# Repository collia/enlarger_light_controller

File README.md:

# enlarger_light_controller

Device that upgrates enlarger head
It based on stm32 blue pill board, spi controlled 7-led indicator, several buttons and encoders, and RGB leds.

It is build in github.com/collia/stm32scons.git environment

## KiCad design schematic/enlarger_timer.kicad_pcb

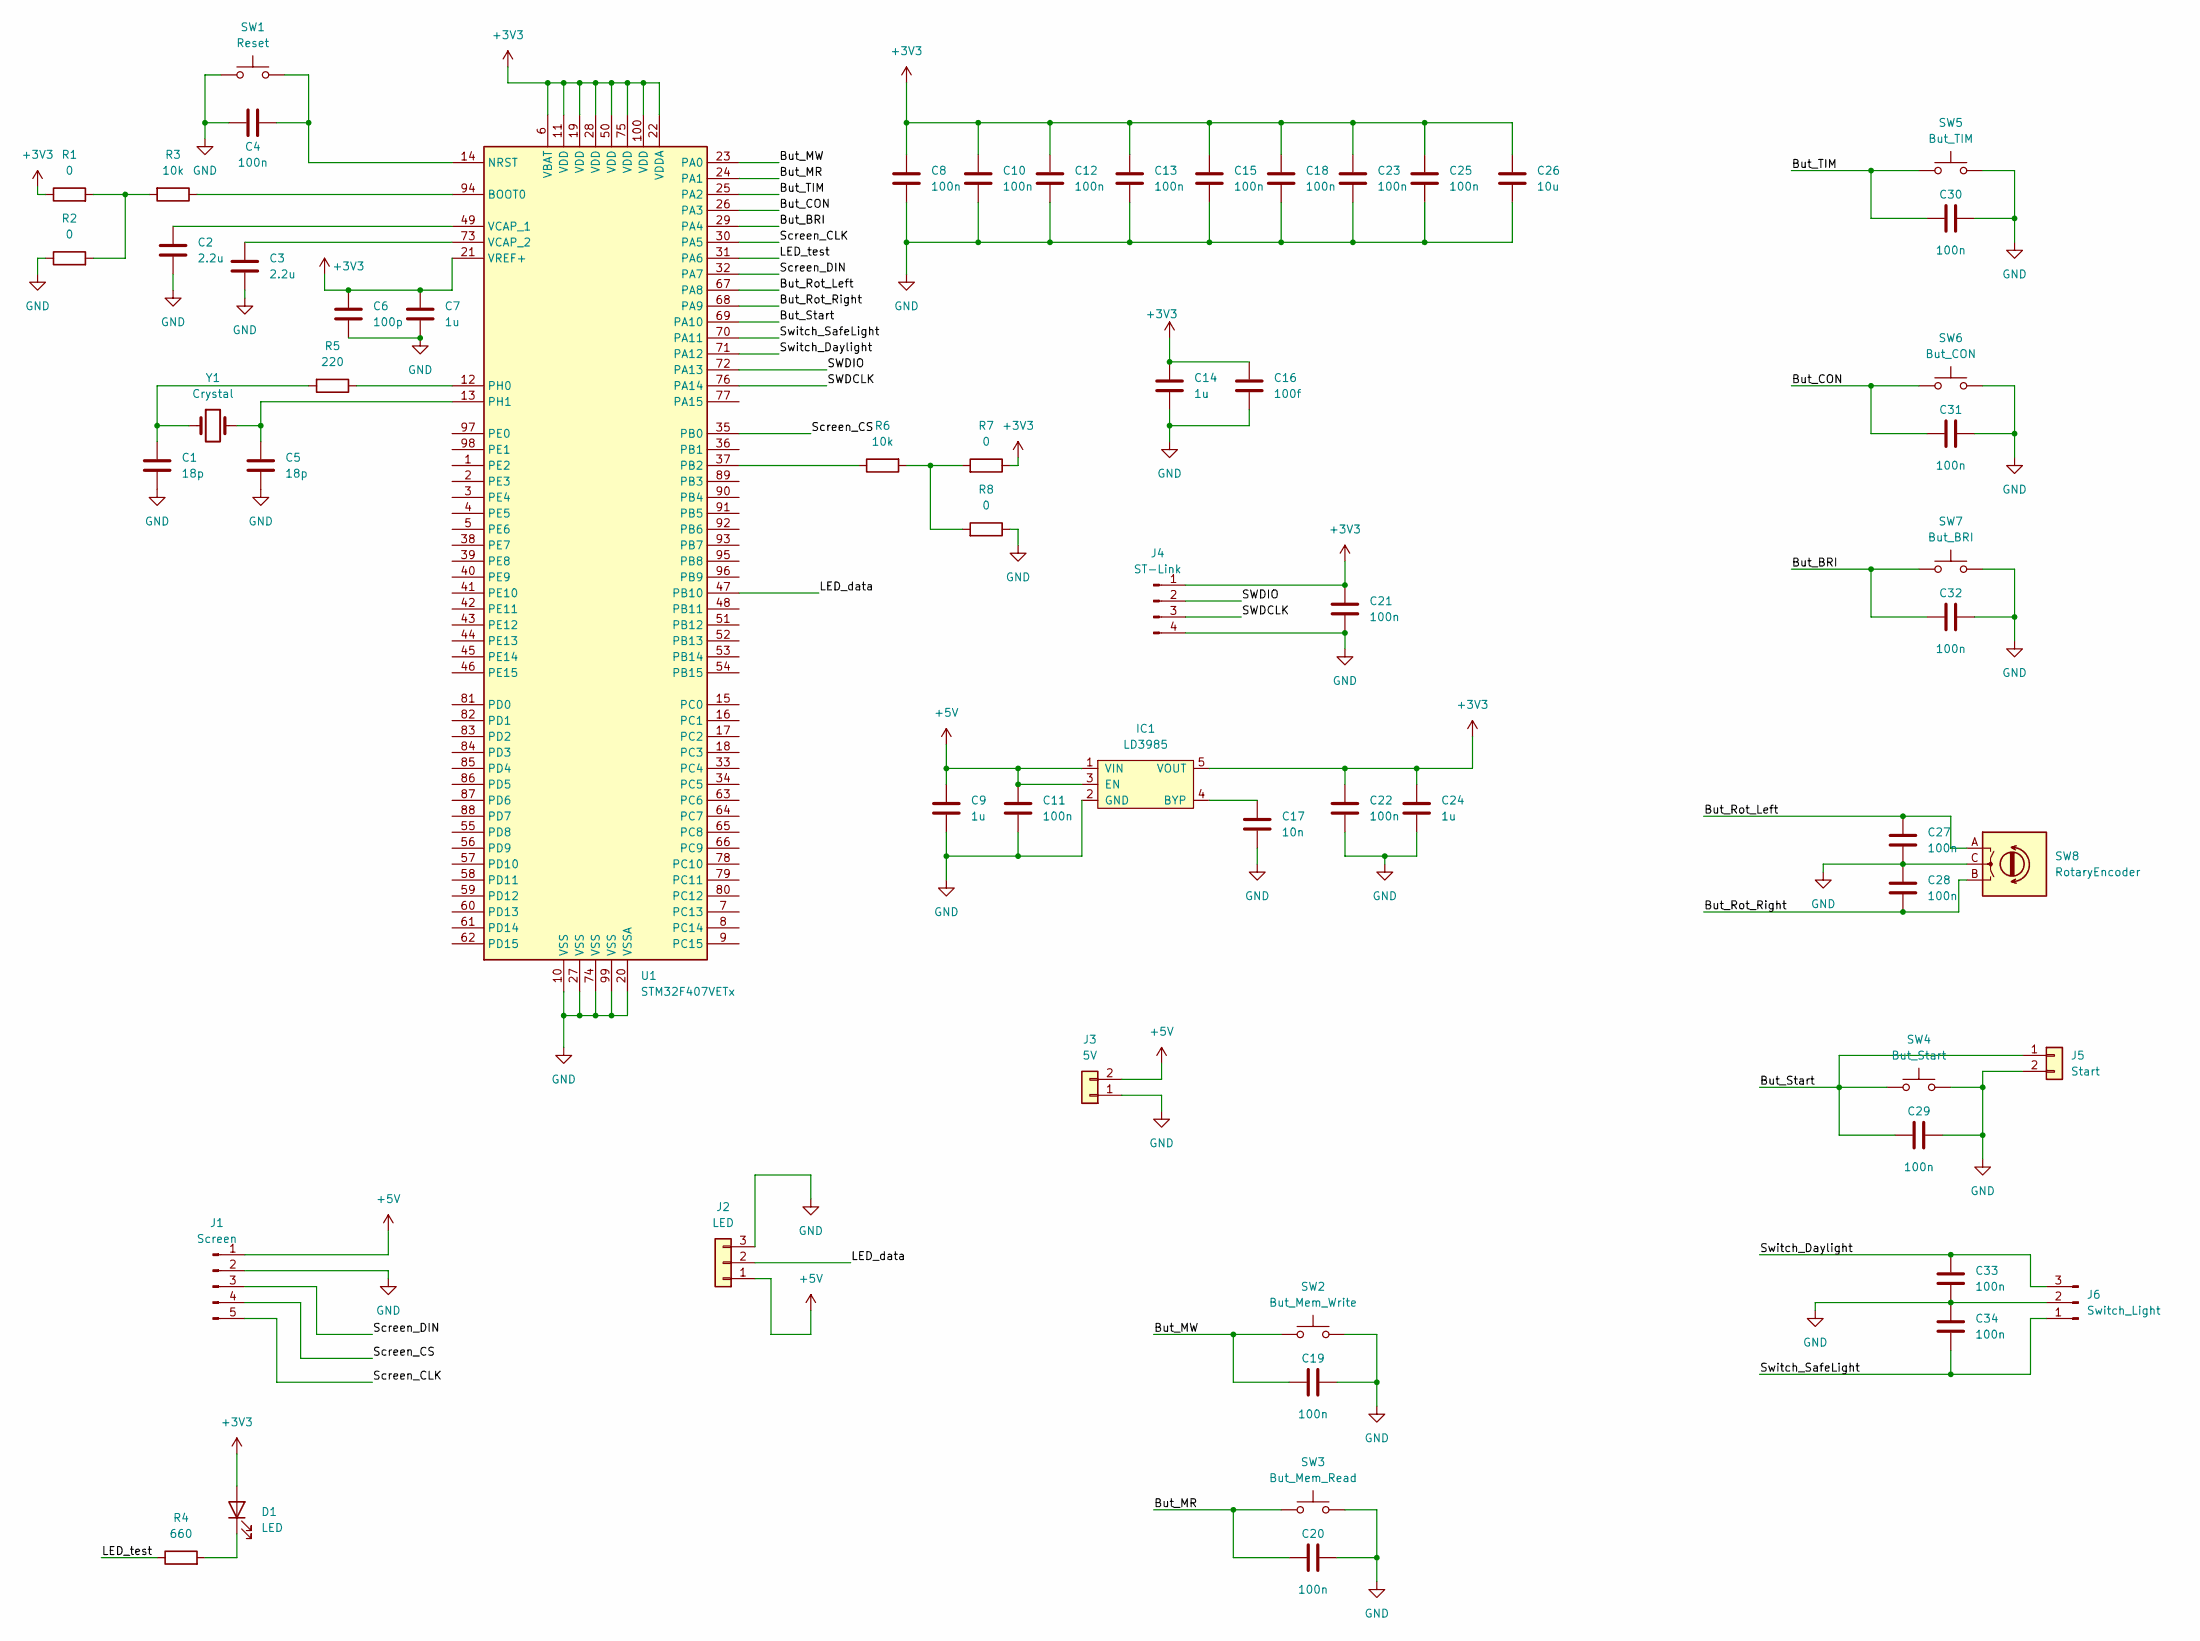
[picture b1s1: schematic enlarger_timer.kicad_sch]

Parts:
C1, C5: 18p; C_0805_2012Metric
C2, C3: 2.2u; C_0805_2012Metric
C4, C8, C10, C11, C12, C13, C15, C18, C19, C20, C21, C22, C23, C25, C27, C28, C29, C30, C31, C32, C33, C34: 100n; C_0805_2012Metric
C6: 100p; C_0805_2012Metric
C7, C9, C14, C24: 1u; C_0805_2012Metric
C16: 100f; C_0805_2012Metric
C17: 10n; C_0805_2012Metric
C26: 10u; C_0805_2012Metric
D1: LED; D_0805_2012Metric
IC1: LD3985; SOT-23-5_HandSoldering; Farnell 3130019
J1: Screen; PinHeader_1x05_P2.54mm_Horizontal
J2: LED; JST_EH_S3B-EH_1x03_P2.50mm_Horizontal
J3: 5V; PinHeader_1x02_P2.54mm_Horizontal
J4: ST-Link; PinHeader_1x04_P2.54mm_Horizontal
J5: Start; JST_EH_S2B-EH_1x02_P2.50mm_Horizontal
J6: Switch_Light; PinHeader_1x03_P2.54mm_Horizontal
R1, R2, R7, R8: 0; R_0805_2012Metric
R3, R6: 10k; R_0805_2012Metric
R4: 660; R_0805_2012Metric
R5: 220; R_0805_2012Metric
SW1: Reset; SW_Push_1P1T_NO_6x6mm_H9.5mm
SW2: But_Mem_Write; SW_Push_1P1T_NO_6x6mm_H9.5mm
SW3: But_Mem_Read; SW_Push_1P1T_NO_6x6mm_H9.5mm
SW4: But_Start; SW_Push_1P1T_NO_6x6mm_H9.5mm
SW5: But_TIM; SW_Push_1P1T_NO_6x6mm_H9.5mm
SW6: But_CON; SW_Push_1P1T_NO_6x6mm_H9.5mm
SW7: But_BRI; SW_Push_1P1T_NO_6x6mm_H9.5mm
SW8: RotaryEncoder; SMD_Encoder
U1: STM32F407VETx; LQFP-100_14x14mm_P0.5mm
Y1: Crystal; Crystal_HC18-U_Vertical

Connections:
+3V3: C6.1, C7.1, C8.1, C10.1, C12.1, C13.1, C14.1, C15.1, C16.1, C18.1, C21.1, C22.1, C23.1, C24.1, C25.1, C26.1, D1.2 (A), IC1.5 (VOUT), J4.1, R1.1, R7.1, U1.6 (VBAT), U1.11 (VDD), U1.19 (VDD), U1.21 (VREF+), U1.22 (VDDA), U1.28 (VDD), U1.50 (VDD), U1.75 (VDD), U1.100 (VDD)
+5V: C9.1, C11.1, IC1.1 (VIN), IC1.3 (EN), J1.1, J2.1, J3.2
/But_BRI: C32.1, SW7.1, U1.29 (PA4)
/But_CON: C31.1, SW6.1, U1.26 (PA3)
/But_MR: C20.1, SW3.1, U1.24 (PA1)
/But_MW: C19.1, SW2.1, U1.23 (PA0)
/But_Rot_Left: C27.1, SW8.A, U1.67 (PA8)
/But_Rot_Right: C28.2, SW8.B, U1.68 (PA9)
/But_Start: C29.1, J5.1, SW4.1, U1.69 (PA10)
/But_TIM: C30.1, SW5.1, U1.25 (PA2)
/LED_data: J2.2, U1.47 (PB10)
/LED_test: R4.1, U1.31 (PA6)
/SWDCLK: J4.3, U1.76 (PA14)
/SWDIO: J4.2, U1.72 (PA13)
/Screen_CLK: J1.5, U1.30 (PA5)
/Screen_CS: J1.4, U1.35 (PB0)
/Screen_DIN: J1.3, U1.32 (PA7)
/Switch_Daylight: C33.1, J6.3, U1.71 (PA12)
/Switch_SafeLight: C34.2, J6.1, U1.70 (PA11)
GND: C1.2, C2.2, C3.2, C4.1, C5.2, C6.2, C7.2, C8.2, C9.2, C10.2, C11.2, C12.2, C13.2, C14.2, C15.2, C16.2, C17.2, C18.2, C19.2, C20.2, C21.2, C22.2, C23.2, C24.2, C25.2, C26.2, C27.2, C28.1, C29.2, C30.2, C31.2, C32.2, C33.2, C34.1, IC1.2 (GND), J1.2, J2.3, J3.1, J4.4, J5.2, J6.2, R2.1, R8.1, SW1.1, SW2.2, SW3.2, SW4.2, SW5.2, SW6.2, SW7.2, SW8.C, U1.10 (VSS), U1.20 (VSSA), U1.27 (VSS), U1.74 (VSS), U1.99 (VSS)
unnamed: C1.1, R5.2, Y1.1
unnamed: C2.1, U1.49 (VCAP_1)
unnamed: C3.1, U1.73 (VCAP_2)
unnamed: C4.2, SW1.2, U1.14 (NRST)
unnamed: C5.1, U1.13 (PH1), Y1.2
unnamed: C17.1, IC1.4 (BYP)
unnamed: D1.1 (K), R4.2
unnamed: R1.2, R2.2, R3.2
unnamed: R3.1, U1.94 (BOOT0)
unnamed: R5.1, U1.12 (PH0)
unnamed: R6.1, U1.37 (PB2)
unnamed: R6.2, R7.2, R8.2

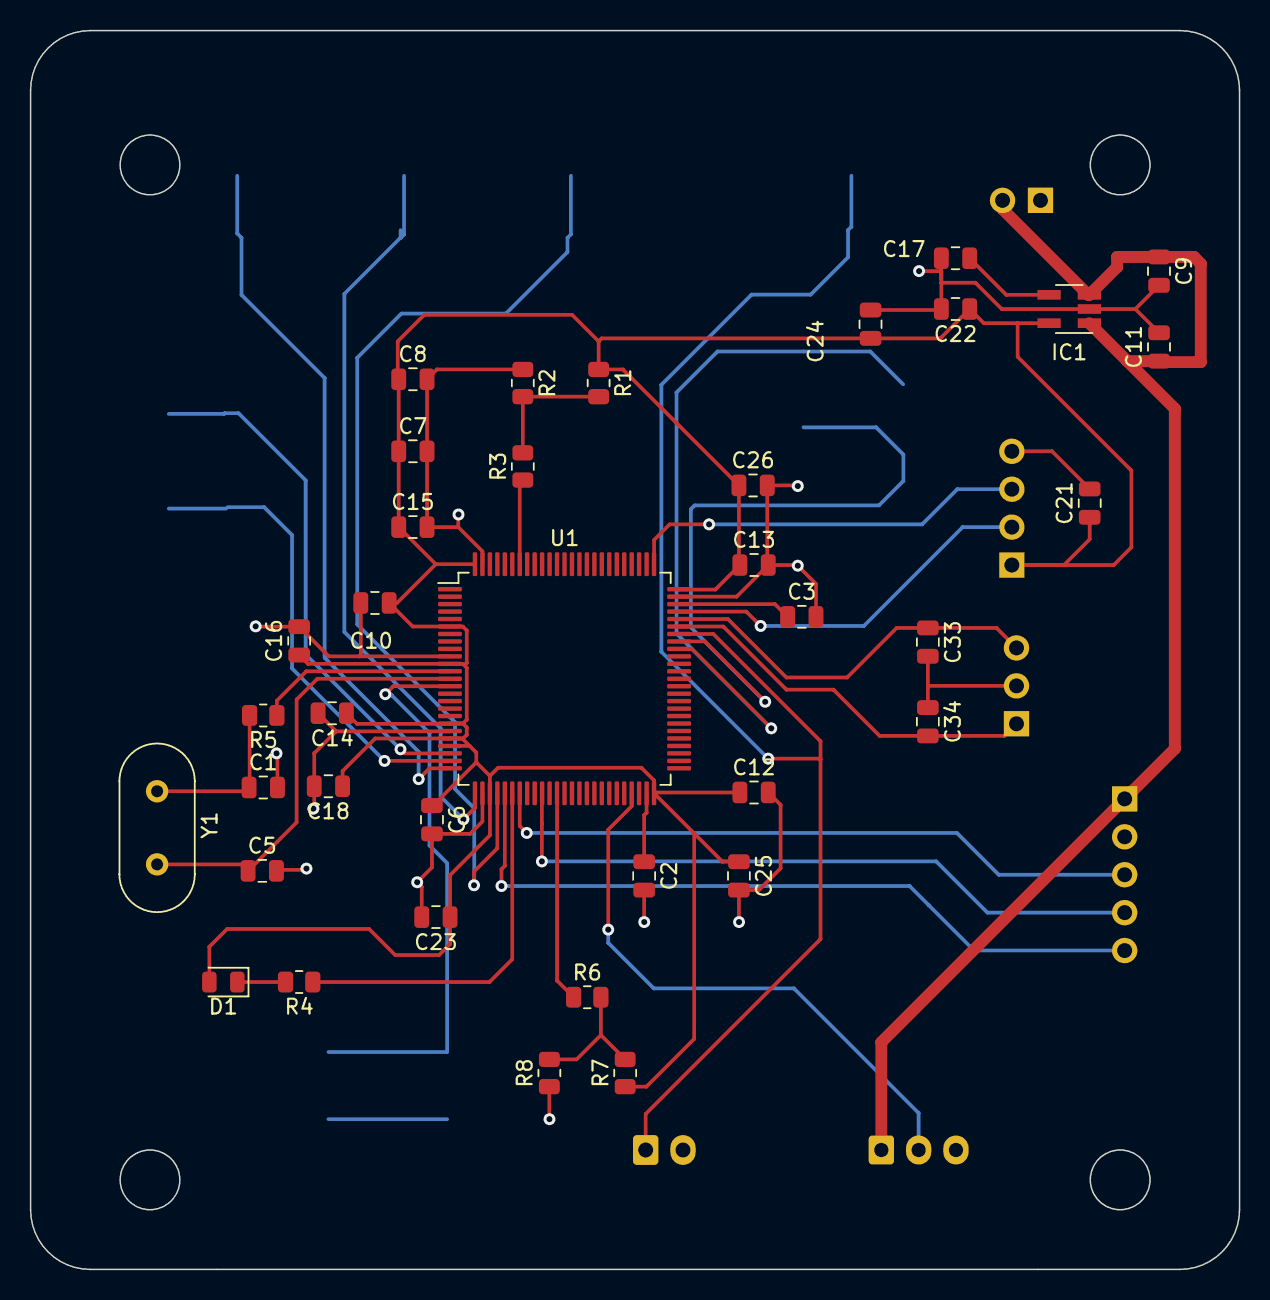
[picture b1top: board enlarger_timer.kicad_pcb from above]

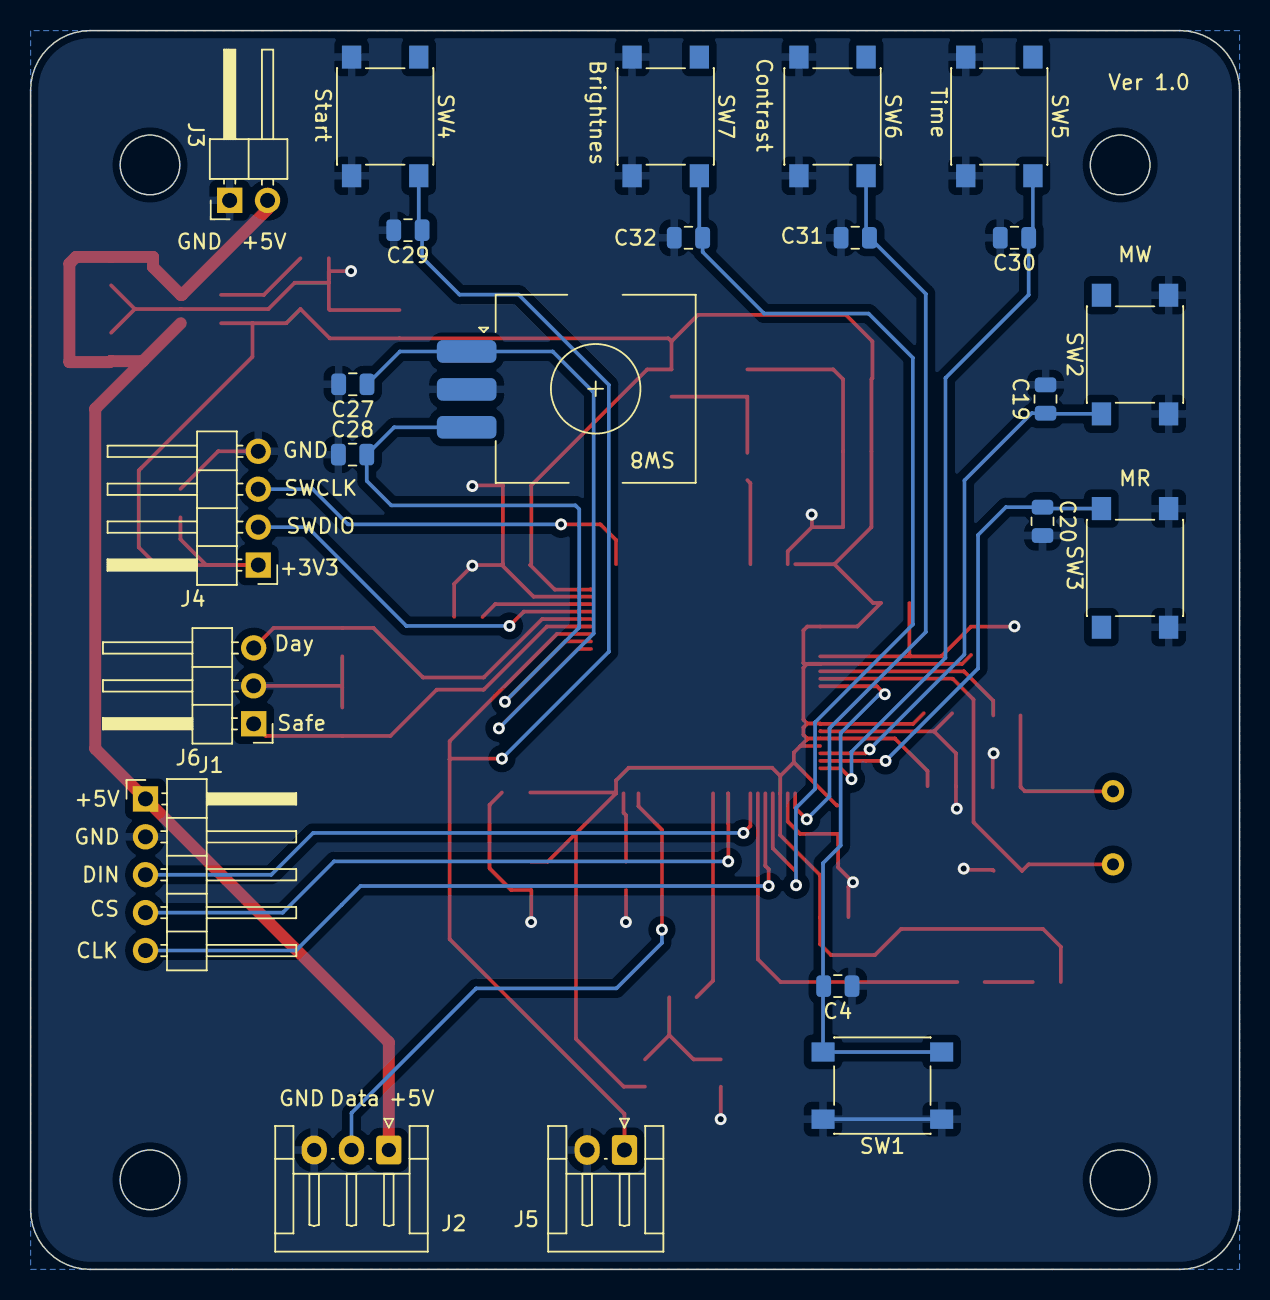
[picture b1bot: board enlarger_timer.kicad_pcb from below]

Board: 2 copper layers, 81.0 x 83.0 mm, 60 parts (23 on the bottom side), 32 nets.

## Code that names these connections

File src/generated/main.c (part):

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  /*Configure GPIO pin Output Level */
  HAL_GPIO_WritePin(GPIOB, GPIO_PIN_0, GPIO_PIN_RESET);

  /*Configure GPIO pins : PA0 PA1 PA2 PA3
                           PA4 PA10 */
  GPIO_InitStruct.Pin = GPIO_PIN_0|GPIO_PIN_1|GPIO_PIN_2|GPIO_PIN_3
                          |GPIO_PIN_4|GPIO_PIN_10;
  GPIO_InitStruct.Mode = GPIO_MODE_IT_RISING;
  GPIO_InitStruct.Pull = GPIO_PULLUP;
  HAL_GPIO_Init(GPIOA, &GPIO_InitStruct);

  /*Configure GPIO pin : PA6 */
  GPIO_InitStruct.Pin = GPIO_PIN_6;
  GPIO_InitStruct.Mode = GPIO_MODE_OUTPUT_PP;
  GPIO_InitStruct.Pull = GPIO_NOPULL;
  GPIO_InitStruct.Speed = GPIO_SPEED_FREQ_LOW;
  HAL_GPIO_Init(GPIOA, &GPIO_InitStruct);

  /*Configure GPIO pin : PB0 */
  GPIO_InitStruct.Pin = GPIO_PIN_0;
  GPIO_InitStruct.Mode = GPIO_MODE_OUTPUT_PP;
  GPIO_InitStruct.Pull = GPIO_PULLDOWN;
  GPIO_InitStruct.Speed = GPIO_SPEED_FREQ_HIGH;
  HAL_GPIO_Init(GPIOB, &GPIO_InitStruct);

  /*Configure GPIO pins : PA11 PA12 */
  GPIO_InitStruct.Pin = GPIO_PIN_11|GPIO_PIN_12;
  GPIO_InitStruct.Mode = GPIO_MODE_IT_RISING_FALLING;
  GPIO_InitStruct.Pull = GPIO_PULLUP;
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
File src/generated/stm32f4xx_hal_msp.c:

/* USER CODE BEGIN Header */
/**
  ******************************************************************************
  * @file         stm32f4xx_hal_msp.c
  * @brief        This file provides code for the MSP Initialization
  *               and de-Initialization codes.
  ******************************************************************************
  * @attention
  *
  * Copyright (c) 2022 STMicroelectronics.
  * All rights reserved.
  *
  * This software is licensed under terms that can be found in the LICENSE file
  * in the root directory of this software component.
  * If no LICENSE file comes with this software, it is provided AS-IS.
  *
  ******************************************************************************
  */
/* USER CODE END Header */

/* Includes ------------------------------------------------------------------*/
#include "main.h"
/* USER CODE BEGIN Includes */

/* USER CODE END Includes */
extern DMA_HandleTypeDef hdma_tim2_up_ch3;

/* Private typedef -----------------------------------------------------------*/
/* USER CODE BEGIN TD */

/* USER CODE END TD */

/* Private define ------------------------------------------------------------*/
/* USER CODE BEGIN Define */

/* USER CODE END Define */

/* Private macro -------------------------------------------------------------*/
/* USER CODE BEGIN Macro */

/* USER CODE END Macro */

/* Private variables ---------------------------------------------------------*/
/* USER CODE BEGIN PV */

/* USER CODE END PV */

/* Private function prototypes -----------------------------------------------*/
/* USER CODE BEGIN PFP */

/* USER CODE END PFP */

/* External functions --------------------------------------------------------*/
/* USER CODE BEGIN ExternalFunctions */

/* USER CODE END ExternalFunctions */

/* USER CODE BEGIN 0 */

/* USER CODE END 0 */

void HAL_TIM_MspPostInit(TIM_HandleTypeDef *htim);
                    /**
  * Initializes the Global MSP.
  */
void HAL_MspInit(void)
{
  /* USER CODE BEGIN MspInit 0 */

  /* USER CODE END MspInit 0 */

  __HAL_RCC_SYSCFG_CLK_ENABLE();
  __HAL_RCC_PWR_CLK_ENABLE();

  /* System interrupt init*/

  /* USER CODE BEGIN MspInit 1 */

  /* USER CODE END MspInit 1 */
}

/**
* @brief SPI MSP Initialization
* This function configures the hardware resources used in this example
* @param hspi: SPI handle pointer
* @retval None
*/
void HAL_SPI_MspInit(SPI_HandleTypeDef* hspi)
{
  GPIO_InitTypeDef GPIO_InitStruct = {0};
  if(hspi->Instance==SPI1)
  {
  /* USER CODE BEGIN SPI1_MspInit 0 */

  /* USER CODE END SPI1_MspInit 0 */
    /* Peripheral clock enable */
    __HAL_RCC_SPI1_CLK_ENABLE();

    __HAL_RCC_GPIOA_CLK_ENABLE();
    /**SPI1 GPIO Configuration
    PA5     ------> SPI1_SCK
    PA7     ------> SPI1_MOSI
    */
    GPIO_InitStruct.Pin = GPIO_PIN_5|GPIO_PIN_7;
    GPIO_InitStruct.Mode = GPIO_MODE_AF_PP;
    GPIO_InitStruct.Pull = GPIO_NOPULL;
    GPIO_InitStruct.Speed = GPIO_SPEED_FREQ_VERY_HIGH;
    GPIO_InitStruct.Alternate = GPIO_AF5_SPI1;
    HAL_GPIO_Init(GPIOA, &GPIO_InitStruct);

    /* SPI1 interrupt Init */
    HAL_NVIC_SetPriority(SPI1_IRQn, 0, 0);
    HAL_NVIC_EnableIRQ(SPI1_IRQn);
  /* USER CODE BEGIN SPI1_MspInit 1 */

  /* USER CODE END SPI1_MspInit 1 */
  }

}

/**
* @brief SPI MSP De-Initialization
* This function freeze the hardware resources used in this example
* @param hspi: SPI handle pointer
* @retval None
*/
void HAL_SPI_MspDeInit(SPI_HandleTypeDef* hspi)
{
  if(hspi->Instance==SPI1)
  {
  /* USER CODE BEGIN SPI1_MspDeInit 0 */

  /* USER CODE END SPI1_MspDeInit 0 */
    /* Peripheral clock disable */
    __HAL_RCC_SPI1_CLK_DISABLE();

    /**SPI1 GPIO Configuration
    PA5     ------> SPI1_SCK
    PA7     ------> SPI1_MOSI
    */
    HAL_GPIO_DeInit(GPIOA, GPIO_PIN_5|GPIO_PIN_7);

    /* SPI1 interrupt DeInit */
    HAL_NVIC_DisableIRQ(SPI1_IRQn);
  /* USER CODE BEGIN SPI1_MspDeInit 1 */

  /* USER CODE END SPI1_MspDeInit 1 */
  }

}

/**
* @brief TIM_Encoder MSP Initialization
* This function configures the hardware resources used in this example
* @param htim_encoder: TIM_Encoder handle pointer
* @retval None
*/
void HAL_TIM_Encoder_MspInit(TIM_HandleTypeDef* htim_encoder)
{
  GPIO_InitTypeDef GPIO_InitStruct = {0};
  if(htim_encoder->Instance==TIM1)
  {
  /* USER CODE BEGIN TIM1_MspInit 0 */

  /* USER CODE END TIM1_MspInit 0 */
    /* Peripheral clock enable */
    __HAL_RCC_TIM1_CLK_ENABLE();

    __HAL_RCC_GPIOA_CLK_ENABLE();
    /**TIM1 GPIO Configuration
    PA8     ------> TIM1_CH1
    PA9     ------> TIM1_CH2
    */
    GPIO_InitStruct.Pin = GPIO_PIN_8|GPIO_PIN_9;
    GPIO_InitStruct.Mode = GPIO_MODE_AF_PP;
    GPIO_InitStruct.Pull = GPIO_PULLUP;
    GPIO_InitStruct.Speed = GPIO_SPEED_FREQ_LOW;
    GPIO_InitStruct.Alternate = GPIO_AF1_TIM1;
    HAL_GPIO_Init(GPIOA, &GPIO_InitStruct);

    /* TIM1 interrupt Init */
    HAL_NVIC_SetPriority(TIM1_CC_IRQn, 0, 0);
    HAL_NVIC_EnableIRQ(TIM1_CC_IRQn);
  /* USER CODE BEGIN TIM1_MspInit 1 */

  /* USER CODE END TIM1_MspInit 1 */
  }

}

/**
* @brief TIM_Base MSP Initialization
* This function configures the hardware resources used in this example
* @param htim_base: TIM_Base handle pointer
* @retval None
*/
void HAL_TIM_Base_MspInit(TIM_HandleTypeDef* htim_base)
{
  if(htim_base->Instance==TIM2)
  {
  /* USER CODE BEGIN TIM2_MspInit 0 */

  /* USER CODE END TIM2_MspInit 0 */
    /* Peripheral clock enable */
    __HAL_RCC_TIM2_CLK_ENABLE();

    /* TIM2 DMA Init */
    /* TIM2_UP_CH3 Init */
    hdma_tim2_up_ch3.Instance = DMA1_Stream1;
    hdma_tim2_up_ch3.Init.Channel = DMA_CHANNEL_3;
    hdma_tim2_up_ch3.Init.Direction = DMA_MEMORY_TO_PERIPH;
    hdma_tim2_up_ch3.Init.PeriphInc = DMA_PINC_DISABLE;
    hdma_tim2_up_ch3.Init.MemInc = DMA_MINC_ENABLE;
    hdma_tim2_up_ch3.Init.PeriphDataAlignment = DMA_PDATAALIGN_WORD;
    hdma_tim2_up_ch3.Init.MemDataAlignment = DMA_MDATAALIGN_WORD;
    hdma_tim2_up_ch3.Init.Mode = DMA_CIRCULAR;
    hdma_tim2_up_ch3.Init.Priority = DMA_PRIORITY_HIGH;
    hdma_tim2_up_ch3.Init.FIFOMode = DMA_FIFOMODE_DISABLE;
    if (HAL_DMA_Init(&hdma_tim2_up_ch3) != HAL_OK)
    {
      Error_Handler();
    }

    /* Several peripheral DMA handle pointers point to the same DMA handle.
     Be aware that there is only one stream to perform all the requested DMAs. */
    __HAL_LINKDMA(htim_base,hdma[TIM_DMA_ID_UPDATE],hdma_tim2_up_ch3);
    __HAL_LINKDMA(htim_base,hdma[TIM_DMA_ID_CC3],hdma_tim2_up_ch3);

  /* USER CODE BEGIN TIM2_MspInit 1 */

  /* USER CODE END TIM2_MspInit 1 */
  }

}

void HAL_TIM_MspPostInit(TIM_HandleTypeDef* htim)
{
  GPIO_InitTypeDef GPIO_InitStruct = {0};
  if(htim->Instance==TIM2)
  {
  /* USER CODE BEGIN TIM2_MspPostInit 0 */

  /* USER CODE END TIM2_MspPostInit 0 */

    __HAL_RCC_GPIOB_CLK_ENABLE();
    /**TIM2 GPIO Configuration
    PB10     ------> TIM2_CH3
    */
    GPIO_InitStruct.Pin = GPIO_PIN_10;
    GPIO_InitStruct.Mode = GPIO_MODE_AF_PP;
    GPIO_InitStruct.Pull = GPIO_NOPULL;
    GPIO_InitStruct.Speed = GPIO_SPEED_FREQ_LOW;
    GPIO_InitStruct.Alternate = GPIO_AF1_TIM2;
    HAL_GPIO_Init(GPIOB, &GPIO_InitStruct);

  /* USER CODE BEGIN TIM2_MspPostInit 1 */

  /* USER CODE END TIM2_MspPostInit 1 */
  }

}
/**
* @brief TIM_Encoder MSP De-Initialization
* This function freeze the hardware resources used in this example
* @param htim_encoder: TIM_Encoder handle pointer
* @retval None
*/
void HAL_TIM_Encoder_MspDeInit(TIM_HandleTypeDef* htim_encoder)
{
  if(htim_encoder->Instance==TIM1)
  {
  /* USER CODE BEGIN TIM1_MspDeInit 0 */

  /* USER CODE END TIM1_MspDeInit 0 */
    /* Peripheral clock disable */
    __HAL_RCC_TIM1_CLK_DISABLE();

    /**TIM1 GPIO Configuration
    PA8     ------> TIM1_CH1
    PA9     ------> TIM1_CH2
    */
    HAL_GPIO_DeInit(GPIOA, GPIO_PIN_8|GPIO_PIN_9);

    /* TIM1 interrupt DeInit */
    HAL_NVIC_DisableIRQ(TIM1_CC_IRQn);
  /* USER CODE BEGIN TIM1_MspDeInit 1 */

  /* USER CODE END TIM1_MspDeInit 1 */
  }

}

/**
* @brief TIM_Base MSP De-Initialization
* This function freeze the hardware resources used in this example
* @param htim_base: TIM_Base handle pointer
* @retval None
*/
void HAL_TIM_Base_MspDeInit(TIM_HandleTypeDef* htim_base)
{
  if(htim_base->Instance==TIM2)
  {
  /* USER CODE BEGIN TIM2_MspDeInit 0 */

  /* USER CODE END TIM2_MspDeInit 0 */
    /* Peripheral clock disable */
    __HAL_RCC_TIM2_CLK_DISABLE();

    /* TIM2 DMA DeInit */
    HAL_DMA_DeInit(htim_base->hdma[TIM_DMA_ID_UPDATE]);
    HAL_DMA_DeInit(htim_base->hdma[TIM_DMA_ID_CC3]);
  /* USER CODE BEGIN TIM2_MspDeInit 1 */

  /* USER CODE END TIM2_MspDeInit 1 */
  }

}

/* USER CODE BEGIN 1 */

/* USER CODE END 1 */

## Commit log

2021-08-22 Copied freertos blinky example
2022-01-15 Added drivers for screen and buttons`
2022-01-15 Removed editor temp files
2022-01-16 Added initial implementation ws2812 driver
2022-01-29 Rewrite 2812 driver - now is storing information about one led in memory
2022-01-30 Added implemetration for light selector
2022-02-12 Initial version for the board schematic
2022-02-12 Added gerber files
2022-02-13 Starting adding initial version of stm32f407 support
2022-02-13 Updated board: change button positions, add conneting holes
2022-02-13 Added legend in silk
2022-02-14 Added stm32f407 initial support - fixed compilation
2022-02-14 Updated schematic: fixed board dimentions
2022-02-16 Added StmCubeMx generated project
2022-02-17 Integrated generated files from mxCube, fixed encodings
2022-02-19 added generated header
2022-02-19 Updated clock config in cobeMx
2022-02-19 Enabled interrupts in mxCube
2022-02-19 Merged GPI IRQ configuration. Buttons is working
2022-02-19 mxCube - enabled all interrupts for TIM1
2022-02-20 mxCube: changed clock configuration - increased core speed
